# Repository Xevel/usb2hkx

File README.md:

usb2hkx
=======

USB interface for Herkulex servos

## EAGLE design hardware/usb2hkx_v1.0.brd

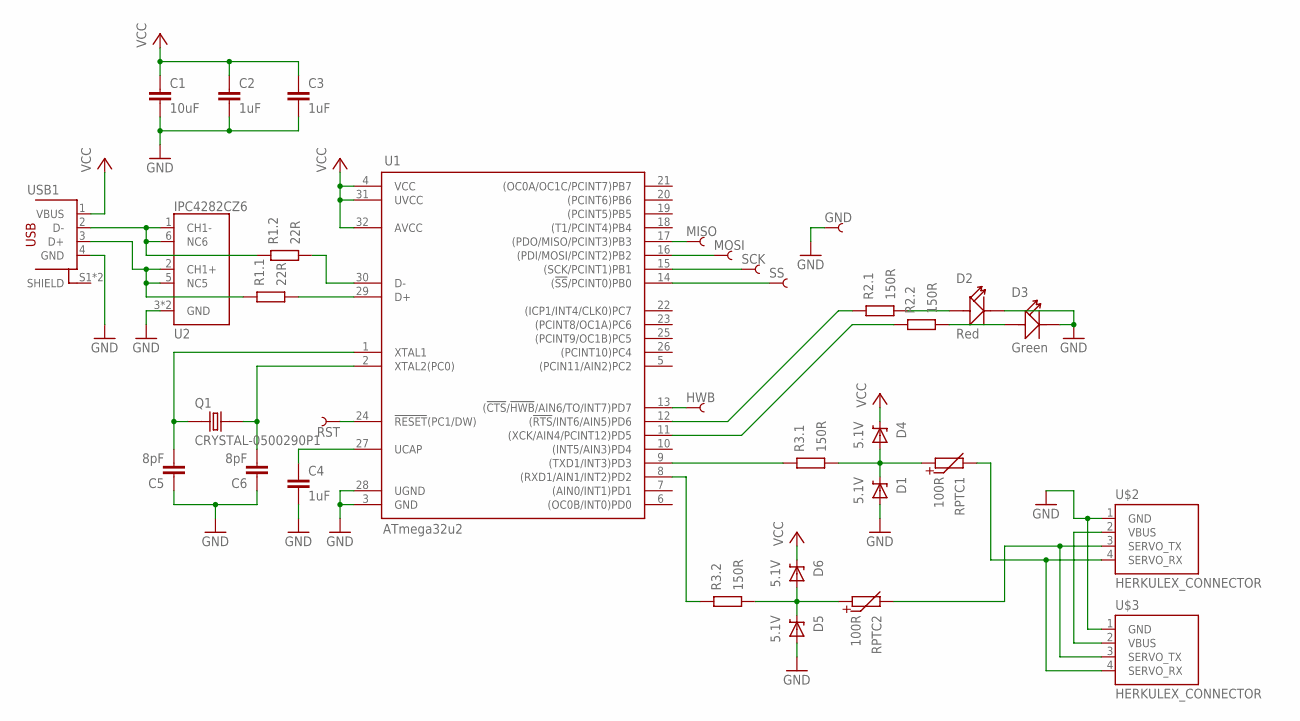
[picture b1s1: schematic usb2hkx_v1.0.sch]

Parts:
C1: 10uF; 0805_L
C2, C3, C4: 1uF; 0402_N
C5, C6: 8pF; 0402_N
D1, D4, D5, D6: 5.1V; SOD-923_N
D2: Red; LED0603
D3: Green; LED0603
GND: PIN_SMD_2X2.5
HWB: PIN_SMD_2X2.5
MISO: PIN_SMD_2X2.5
MOSI: PIN_SMD_2X2.5
Q1: CRYSTAL-0500290P1; 2P-SMD-5.0X3.2
R1: 22R; ARRAY_0402_65P_2_N
R2, R3: 150R; ARRAY_0402_65P_2_N
RPTC1, RPTC2: 100R; 0603_N
RST: PIN_SMD_2X2.5
SCK: PIN_SMD_2X2.5
SS: PIN_SMD_2X2.5
U1: ATmega32u2; QFN-32_50P_L_MOD
U2: IPC4282CZ6; XSON6_N
U$2, U$3: HERKULEX_CONNECTOR; YW200-04
USB1: USB-STANDARD-PLUG_A_THT; USB-A-THT

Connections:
GND: C1.2, C2.2, C3.2, C4.2, C5.1, C6.1, D1.A, D2.-, D3.-, D5.A, GND.PIN, U1.3 (GND), U1.28 (UGND), U2.3 (GND), U2.4 (GND), U$2.1 (GND), U$3.1 (GND), USB1.4 (GND)
HWB: HWB.PIN, U1.13 ((!CTS!/!HWB!/AIN6/TO/INT7)PD7)
unnamed: R3.3 (2), U1.9 ((TXD1/INT3)PD3)
unnamed: R3.4 (2), U1.8 ((RXD1/AIN1/INT2)PD2)
unnamed: C4.1, U1.27 (UCAP)
unnamed: R2.3 (2), U1.12 ((!RTS!/INT6/AIN5)PD6)
unnamed: R2.4 (2), U1.11 ((XCK/AIN4/PCINT12)PD5)
unnamed: D1.C, D4.A, R3.2 (1), RPTC1.1
unnamed: C6.2, Q1.2, U1.2 (XTAL2(PC0))
unnamed: C5.2, Q1.1, U1.1 (XTAL1)
unnamed: R1.1, U1.30 (D-)
unnamed: R1.2 (1), U1.29 (D+)
unnamed: R1.4 (2), U2.1 (CH1-), U2.6 (NC6), USB1.2 (D-)
unnamed: R1.3 (2), U2.2 (CH1+), U2.5 (NC5), USB1.3 (D+)
unnamed: D2.+, R2.2 (1)
unnamed: U$2.2 (VBUS), U$3.2 (VBUS)
unnamed: D3.+, R2.1
unnamed: MISO.PIN, U1.17 ((PDO/MISO/PCINT3)PB3)
unnamed: MOSI.PIN, U1.16 ((PDI/MOSI/PCINT2)PB2)
unnamed: SCK.PIN, U1.15 ((SCK/PCINT1)PB1)
unnamed: SS.PIN, U1.14 ((!SS!/PCINT0)PB0)
unnamed: D5.C, D6.A, R3.1, RPTC2.1
RST: RST.PIN, U1.24 (!RESET!(PC1/DW))
RX: RPTC1.2, U$2.4 (SERVO_RX), U$3.4 (SERVO_RX)
TX: RPTC2.2, U$2.3 (SERVO_TX), U$3.3 (SERVO_TX)
VCC: C1.1, C2.1, C3.1, D4.C, D6.C, U1.4 (VCC), U1.31 (UVCC), U1.32 (AVCC), USB1.1 (VBUS)

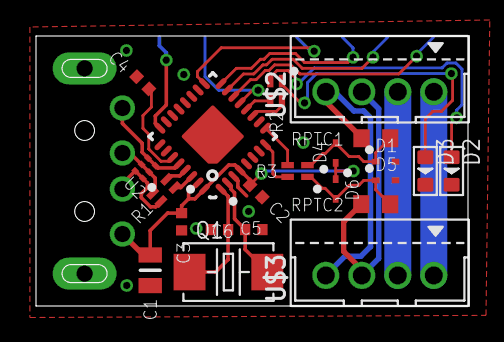
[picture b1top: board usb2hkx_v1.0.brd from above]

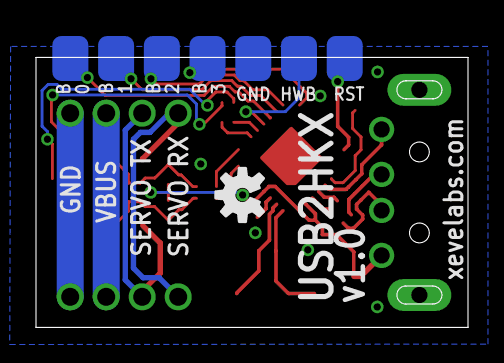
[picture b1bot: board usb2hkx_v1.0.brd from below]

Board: 2 copper layers, 24.0 x 15.0 mm, 31 parts (8 on the bottom side), 26 nets.

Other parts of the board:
U$1: OSHW-LOGO-S

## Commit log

2014-09-15 Initial version of USB to HerKuleX (USB2HKX) interface.

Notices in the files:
parts and their libraries:
SparkFun-Aesthetics: Licensing: CC v3.0 Share-Alike You are welcome to use this library for commercial purposes.
